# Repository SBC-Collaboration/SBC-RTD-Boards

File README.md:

# RTD Boards for SBC

This projects includes all the KiCAD files that can be then exported to gerber. 

It also includes the LTSpice simulations with brief comments on how some parts work.

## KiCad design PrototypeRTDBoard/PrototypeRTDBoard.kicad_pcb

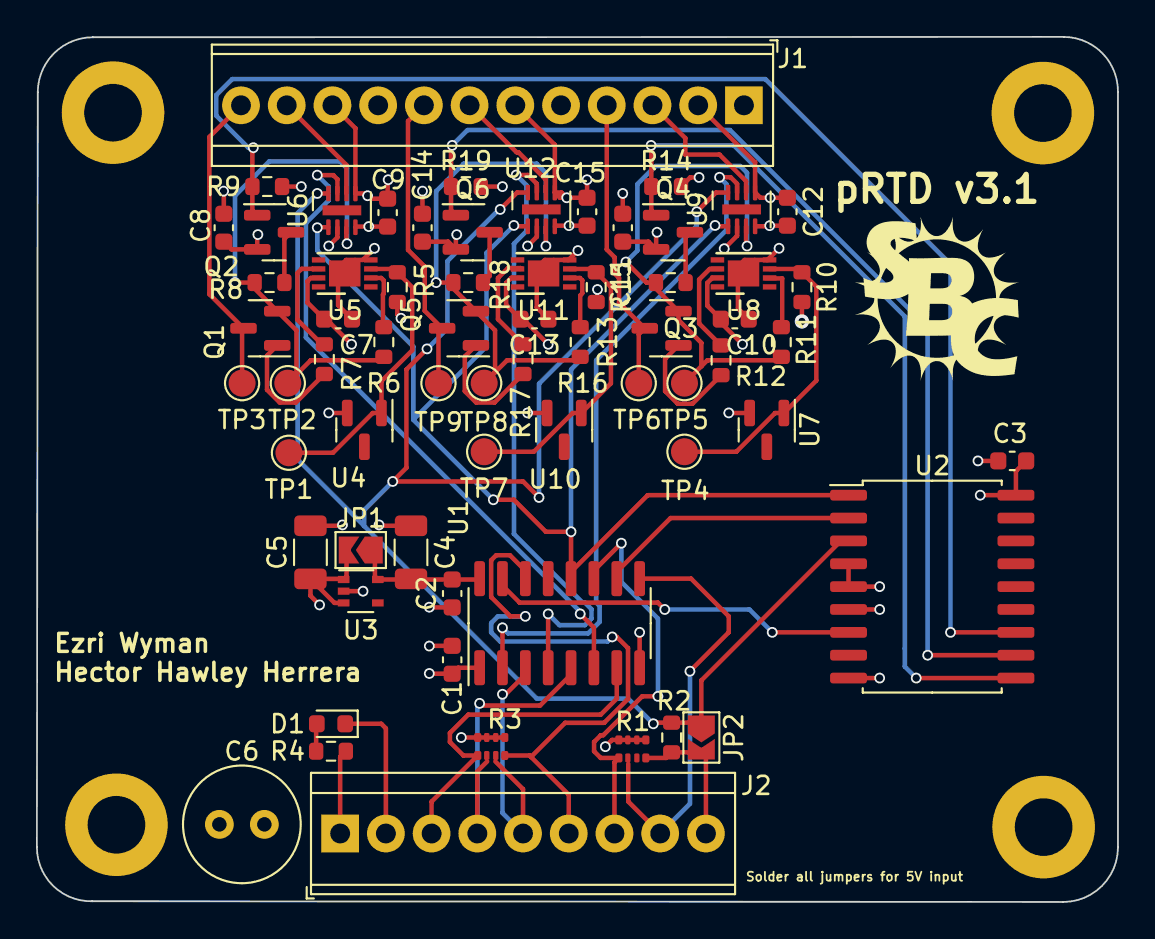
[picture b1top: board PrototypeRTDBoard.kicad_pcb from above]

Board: 4 copper layers, 60.1 x 48.1 mm, 71 parts (0 on the bottom side), 45 nets.

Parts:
C1, C2, C3, C7, C8, C9, C10, C11, C12, C13, C14, C15: 100nF; C_0603_1608Metric
C4, C5: 1 uF; C_1206_3216Metric
C6: 10uF; C_Radial_D6.3mm_H11.0mm_P2.50mm
D1: LED; LED_0603_1608Metric
H1, H2, H3, H4: MountingHole; MountingHole_3.2mm_M3_ISO7380_Pad
J1: Screw_Terminal_01x12; TerminalBlock_TE_1-282834-2_1x12_P2.54mm_Horizontal
J2: Screw_Terminal_01x09; TerminalBlock_TE_282834-9_1x09_P2.54mm_Horizontal
JP1, JP2: SolderJumper_2_Open; SolderJumper-2_P1.3mm_Open_TrianglePad1.0x1.5mm
Q1, Q2, Q3, Q4, Q5, Q6: DMG2301L-7; SOT-23
R1, R3: CAY10-102J4LF; 8-RES-NETWORK
R2: 576; R_0603_1608Metric
R4, R5, R6, R7, R9, R10, R11, R12, R14, R15, R16, R17, R19: 1k; R_0603_1608Metric
R8, R13, R18: 120; R_0603_1608Metric
TP1, TP2, TP3, TP4, TP5, TP6, TP7, TP8, TP9: TestPoint; TestPoint_Pad_D1.5mm
U1: HCF4010YM013TR; SOIC-16_3.9x9.9mm_P1.27mm
U2: MCP23S08; SOIC-18W_7.5x11.6mm_P1.27mm
U3: MIC5365-3.3YC5; SOT-353_SC-70-5
U4, U7, U10: LM4040EIM3-2.5/NOPB; SOT-23
U5, U8, U11: MCP6231-E/MC; DFN-8-1EP_3x2mm_P0.5mm_EP1.75x1.45mm
U6, U9, U12: LTC2452IDDB#TRMPBF; DFN-8-1EP_2x3mm_P0.5mm_EP0.56x2.15mm
X1: Logo; sbc_silk_mask

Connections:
+3V3: C2.2, C4.1, JP1.1 (A), U1.16 (VDD), U3.5 (VOUT)
+5V: C1.2, C3.1, C5.1, C6.1, C7.2, C8.2, C9.1, C10.2, C11.2, C12.1, C13.2, C14.2, C15.1, J2.1, JP1.2 (B), Q2.2 (S), Q4.2 (S), Q6.2 (S), R3.1, R3.2, R3.3, R3.4, R4.1, R5.1, R10.1, R15.1, U1.1 (VCC), U2.6 (RESET), U2.18 (VDD), U3.1 (VIN), U3.3 (EN), U5.7 (VDD), U6.4 (Vcc), U8.7 (VDD), U9.4 (Vcc), U11.7 (VDD), U12.4 (Vcc)
/RTD FRONT END1/Force+: J1.8, Q5.3 (D), TP9.1
/RTD FRONT END1/V+: J1.7, U12.6 (IN+)
/RTD FRONT END1/Vref: Q5.2 (S), R16.1, R18.2, TP8.1, U12.3 (REF)
/RTD FRONT END2/Force+: J1.4, Q3.3 (D), TP6.1
/RTD FRONT END2/V+: J1.3, U9.6 (IN+)
/RTD FRONT END2/Vref: Q3.2 (S), R11.1, R13.2, TP5.1, U9.3 (REF)
/RTD FRONT END/Force+: J1.12, Q1.3 (D), TP3.1
/RTD FRONT END/V+: J1.11, U6.6 (IN+)
/RTD FRONT END/Vref: Q1.2 (S), R6.1, R8.2, TP2.1, U6.3 (REF)
CS0: U1.6 (I=C), U6.7 (CS)
CS0_IN: J2.3, R3.5, U1.7 (C)
CS1: U1.4 (H=B), U12.7 (CS)
CS1_IN: J2.4, R3.6, U1.5 (B)
CS2: U1.2 (G=A), U9.7 (CS)
CS2_IN: J2.5, R3.7, U1.3 (A)
EN0: Q2.1 (G), R9.1, U2.12 (GP2)
EN1: Q6.1 (G), R19.1, U2.11 (GP1)
EN2: Q4.1 (G), R14.1, U2.10 (GP0)
GND: C1.1, C2.1, C3.2, C4.2, C5.2, C6.2, C7.1, C8.1, C9.2, C10.1, C11.1, C12.2, C13.1, C14.1, C15.2, D1.1 (K), J1.1, J1.2, J1.5, J1.6, J1.9, J1.10, J2.2, R1.1, R1.2, R1.3, R1.4, R9.2, R14.2, R19.2, U1.8 (VSS), U2.4 (A1), U2.5 (A0), U2.9 (Vss), U3.2 (GND), U4.2 (A), U5.4 (VSS), U5.9 (EPAD), U6.2 (GND), U6.5 (IN-), U7.2 (A), U8.4 (VSS), U8.9 (EPAD), U9.2 (GND), U9.5 (IN-), U10.2 (A), U11.4 (VSS), U11.9 (EPAD), U12.2 (GND), U12.5 (IN-)
MISO: JP2.1 (A), R2.2, U2.3 (SO), U6.8 (SDO), U9.8 (SDO), U12.8 (SDO)
MISO_OUT: J2.9, JP2.2 (B), R1.8, R2.1
MOSI: U1.10 (J=D), U2.2 (SI)
MOSI_IN: J2.8, R1.6, U1.9 (D)
MULTI_CS: U1.15 (L=F), U2.7 (CS)
MULTI_CS_IN: J2.6, R3.8, U1.14 (F)
unnamed: D1.2 (A), R4.2
unnamed: Q1.1 (G), R7.1
unnamed: Q2.3 (D), R8.1
unnamed: Q3.1 (G), R12.1
unnamed: Q4.3 (D), R13.1
unnamed: Q5.1 (G), R17.1
unnamed: Q6.3 (D), R18.1
unnamed: R5.2, TP1.1, U4.1 (K), U5.3 (VIN+)
unnamed: R6.2, U5.2 (VIN-)
unnamed: R7.2, U5.6 (VOUT)
unnamed: R10.2, TP4.1, U7.1 (K), U8.3 (VIN+)
unnamed: R11.2, U8.2 (VIN-)
unnamed: R12.2, U8.6 (VOUT)
unnamed: R15.2, TP7.1, U10.1 (K), U11.3 (VIN+)
unnamed: R16.2, U11.2 (VIN-)
unnamed: R17.2, U11.6 (VOUT)
SCK: U1.12 (K=E), U2.1 (SCK), U6.1 (SCK), U9.1 (SCK), U12.1 (SCK)
SCK_IN: J2.7, R1.5, U1.11 (E)

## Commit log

2022-09-06 Moving to git as the project keeps changing and more things to come.
